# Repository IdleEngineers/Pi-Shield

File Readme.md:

# Pi Shield

This work is licensed under the Creative Commons Attribution-ShareAlike 4.0 International License. To view a copy of this license, visit http://creativecommons.org/licenses/by-sa/4.0/.

## Here Be Dragons

We want to get the project in front of people, but be warned, we have bugs in our current design. Version 1.0.0 is only partially functional due to some physical problems in our design.

We are currently troubleshooting the problems and fixing the design for version 1.1.0. You can see current details by following our [Pi Shield blog](http://idle.to/1).

## Precursor

This project is just getting off the ground, so please bear with us as we develop the documentation and get the source files online. Thanks!

## The Project

Pi Shield is an open source expansion to the Raspberry Pi ensuring that technological knowledge is accessible to everyone. Providing new functionality and expanded I/O access.

## Usage

TODO: Write section

## Contributing

1. Fork it ( http://github.com/<my-github-username>/Pi-Shield/fork )
2. Create your feature branch (`git checkout -b my-new-feature`)
3. Commit your changes (`git commit -am 'Add some feature'`)
4. Push to the branch (`git push origin my-new-feature`)
5. Create new Pull Request

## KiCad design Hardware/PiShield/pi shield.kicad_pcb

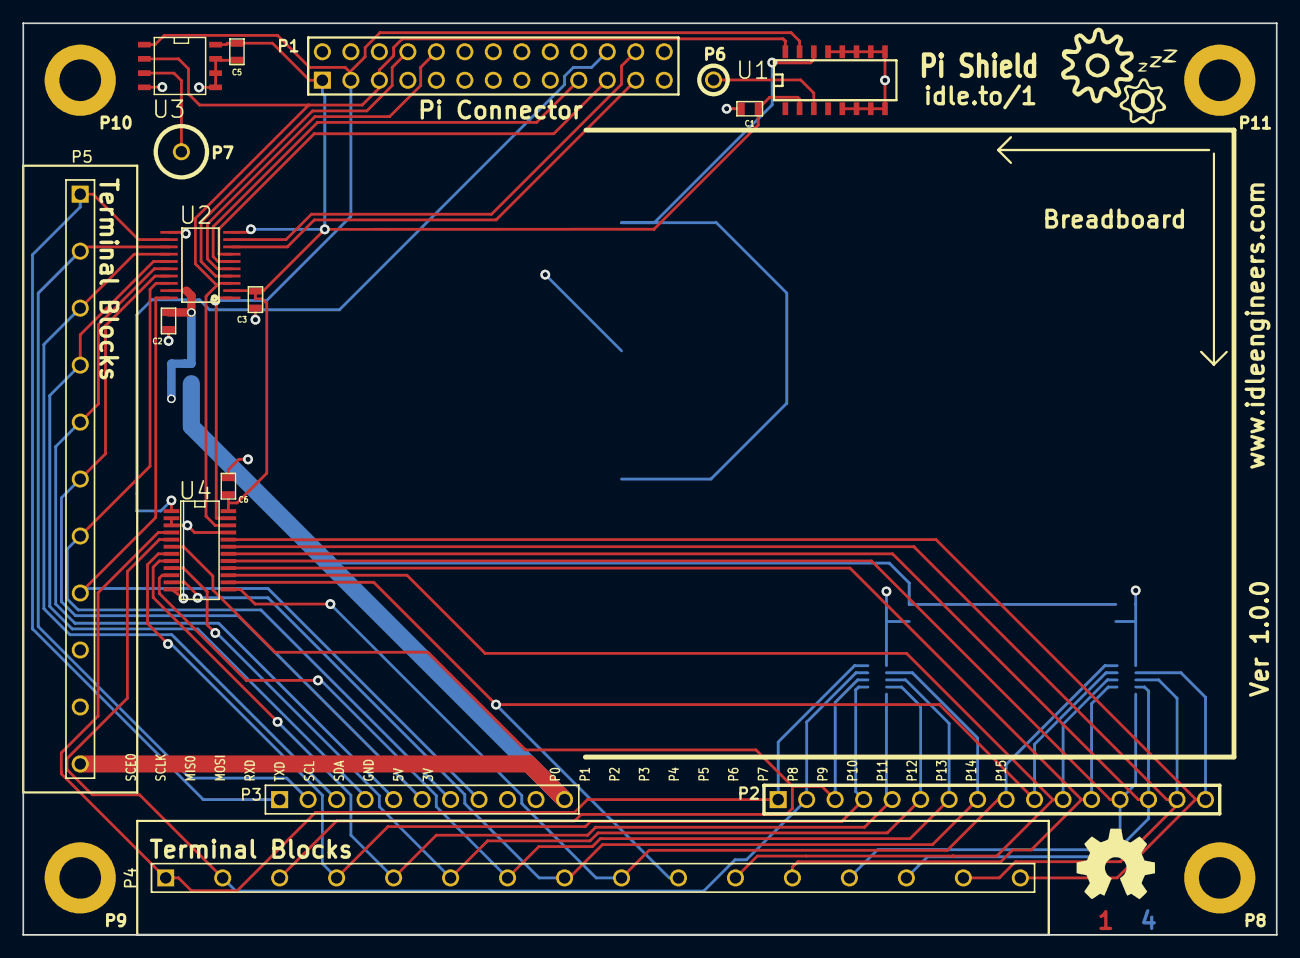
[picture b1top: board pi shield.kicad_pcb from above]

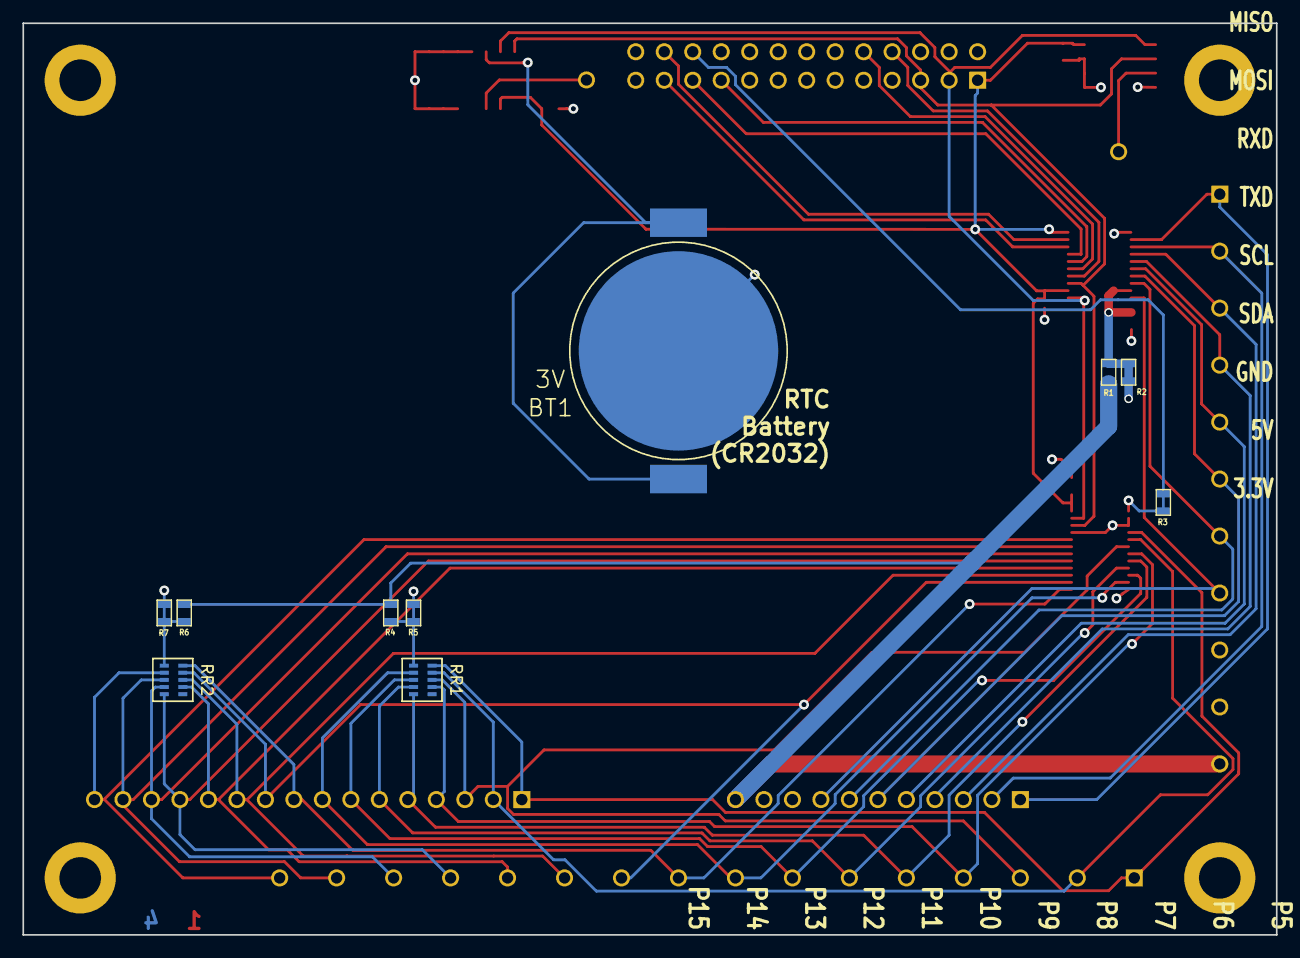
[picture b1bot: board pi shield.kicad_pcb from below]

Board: 4 copper layers, 111.8 x 81.3 mm, 30 parts (10 on the bottom side), 40 nets.

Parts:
BT1: 3V; BAT-HLD-CR2032-on-board
C1, C2, C3, C5, C6: 1uF; SM0603
P1: CONN_13X2; pin_array_13x2
P2: CONN_16; PIN_ARRAY_16x1
P3: CONN_11; PIN_ARRAY_11x1
P4: CONN_16; PIN_ARRAY_16x1_0-2in
P5: CONN_11; PIN_ARRAY_11x1_0-2in
P6, P7: CONN_1; 1pin
P8, P9, P10, P11: CONN_1; 1pin-no-silk
R1, R2, R3, R4, R5, R6, R7: 0; SM0603
RR1, RR2: 10k; R_10k_bus_8qty
U1: DS3231; SO16E
U2: TXB0108; TSSOP_PW_20
U3: DS7505; SO8N
U4: MAX7313AEG; SSOP24

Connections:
3.3VB: P3.11, P5.11, R1.1, R4.1, R6.1
+3.3V: C1.1, C3.2, C5.1, C6.2, P1.1, U1.2, U2.2, U2.10, U3.8, U4.24
+5V: C2.2, P1.2, P1.4, P3.10, P5.10, R1.2, R2.1, R2.2, R4.2, R5.1, R5.2, R6.2, R7.1, R7.2, RR1.1, RR2.1, U2.19
GND: BT1.2, C1.2, C2.1, C3.1, C5.2, C6.1, P1.6, P1.9, P1.14, P3.9, P5.9, P8.1, P9.1, P10.1, P11.1, U1.5, U1.6, U1.7, U1.8, U1.9, U1.10, U1.11, U1.12, U1.13, U2.11, U3.4, U3.5, U3.6, U3.7, U4.2, U4.3, U4.12, U4.21
GPIO_25: P1.22, R3.1, R3.2, U4.1
INT_U1: P6.1, U1.3
MISO: P1.21, U2.7
MOSI: P1.19, U2.6
unnamed: BT1.1, U1.14
O.S.: P7.1, U3.3
P0: P2.1, P4.1, RR1.6, U4.4
P1: P2.2, P4.2, RR1.7, U4.5
P2: P2.3, P4.3, RR1.8, U4.6
P3: P2.4, P4.4, RR1.9, U4.7
P4: P2.5, P4.5, RR1.5, U4.8
P5: P2.6, P4.6, RR1.4, U4.9
P6: P2.7, P4.7, RR1.3, U4.10
P7: P2.8, P4.8, RR1.2, U4.11
P8: P2.9, P4.9, RR2.6, U4.13
P9: P2.10, P4.10, RR2.7, U4.14
P10: P2.11, P4.11, RR2.8, U4.15
P11: P2.12, P4.12, RR2.9, U4.16
P12: P2.13, P4.13, RR2.5, U4.17
P13: P2.14, P4.14, RR2.4, U4.18
P14: P2.15, P4.15, RR2.3, U4.19
P15: P2.16, P4.16, RR2.2, U4.20
RXD: P1.10, U2.5
SCE0: P1.24, U2.9
SCL: P1.5, U1.16, U2.3, U3.2, U4.22
SCLK: P1.23, U2.8
SDA: P1.3, U1.15, U2.1, U3.1, U4.23
TXD: P1.8, U2.4
U_MISO: P3.3, P5.3, U2.14
U_MOSI: P3.4, P5.4, U2.15
U_RXD: P3.5, P5.5, U2.16
U_SCE0: P3.1, P5.1, U2.12
U_SCL: P3.7, P5.7, U2.18
U_SCLK: P3.2, P5.2, U2.13
U_SDA: P3.8, P5.8, U2.20
U_TXD: P3.6, P5.6, U2.17

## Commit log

2014-06-21 Creating repository
2014-07-14 1.0.0 release
